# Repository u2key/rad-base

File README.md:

The PCB for LSI radiation irradiation test.
---

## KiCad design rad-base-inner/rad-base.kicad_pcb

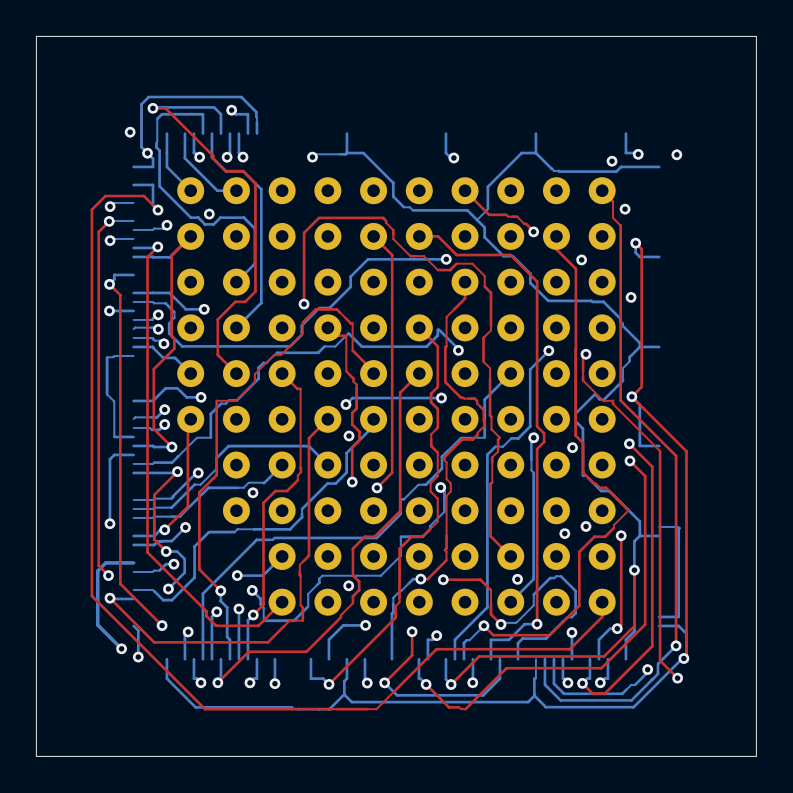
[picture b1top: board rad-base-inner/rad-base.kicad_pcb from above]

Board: 4 copper layers, 40.0 x 40.0 mm, 15 parts (1 on the bottom side), 90 nets.

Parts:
U1: S1D13513F01A100; QFP208-28X28MM
U2, U3, U4: 2x1
U5, U6, U7, U8, U9, U10, U11, U12, U13, U14, U15: 8x1

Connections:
GND: U1.2 (DB14), U1.12 (DB6), U1.22 (~WE0), U1.31 (~WAIT), U1.41 (OSCO1), U1.51 (VCP2(NC)), U1.54 (FPDAT16), U1.64 (FPDAT8), U1.74 (FPDAT0), U1.83 (GPIOG2), U1.93 (GPIOB7), U1.103 (TDO), U1.106 (GND@8), U1.116 (GPIOD2), U1.126 (CNF4), U1.135 (MEMDQM1), U1.145 (MEMBA0), U1.155 (MEMDQ12), U1.158 (MEMDQ11), U1.168 (HVDD5@4), U1.178 (MEMA5), U1.187 (AB18), U1.197 (GND@17), U1.207 (AB0), U2.1 (A1), U2.2 (A2)
VCC1: U1.1 (DB15), U1.21 (BUSCLK), U1.42 (OSCGND1), U1.53 (FPDAT17), U1.73 (FPDAT1), U1.94 (GPIOB6), U1.105 (HVDD4@1), U1.125 (CNF5), U1.146 (MEMA11), U1.157 (COREVDD@6), U1.177 (MEMA6), U1.198 (AB9), U3.1 (A1), U3.2 (A2)
VCC2: U1.11 (DB7), U1.32 (~RESET), U1.52 (PLLGND2), U1.63 (FPDAT9), U1.84 (GPIOG1), U1.104 (TRST), U1.115 (GPIOD3), U1.136 (MEMDQM0), U1.156 (COREVDD@5), U1.167 (MEMDQ4), U1.188 (AB17), U1.208 (COREVDD@7), U4.1 (A1), U4.2 (A2)
w1: U1.3 (DB13), U5.1 (A1)
w2: U1.4 (DB12), U5.2 (A2)
w3: U1.5 (DB11), U5.3 (A3)
w4: U1.6 (DB10), U5.4 (A4)
w5: U1.7 (DB9), U5.5 (A5)
w6: U1.8 (DB8), U5.6 (A6)
w7: U1.9 (HVDD1@0), U5.7 (A7)
w8: U1.10 (GND@0), U5.8 (A8)
w9: U1.13 (DB5), U6.1 (A1)
w10: U1.14 (DB4), U6.2 (A2)
w11: U1.15 (DB3), U6.3 (A3)
w12: U1.16 (DB2), U6.4 (A4)
w13: U1.17 (DB1), U6.5 (A5)
w14: U1.18 (DB0), U6.6 (A6)
w15: U1.19 (HVDD1@1), U6.7 (A7)
w16: U1.20 (GND@1), U6.8 (A8)
w17: U1.23 (~WE1), U7.1 (A1)
w18: U1.24 (M/~R), U7.2 (A2)
w19: U1.25 (~CS), U7.3 (A3)
w20: U1.26 (~BS), U7.4 (A4)
w21: U1.27 (RD/~WR), U7.5 (A5)
w22: U1.28 (~RD), U7.6 (A6)
w23: U1.29 (COREVDD@0), U7.7 (A7)
w24: U1.30 (~INT1), U7.8 (A8)
w26: U1.34 (~BURST), U8.2 (A2)
w27: U1.35 (~BDIP), U8.3 (A3)
w28: U1.36 (CLKI3), U8.4 (A4)
w29: U1.37 (COREVDD@1), U8.5 (A5)
w30: U1.38 (GND@2), U8.6 (A6)
w31: U1.39 (OSCVDD1), U8.7 (A7)
w32: U1.40 (OSCI1), U8.8 (A8)
w33: U1.43 (OSCGND2), U9.1 (A1)
w34: U1.44 (OSCO2), U9.2 (A2)
w35: U1.45 (OSCI2), U9.3 (A3)
w36: U1.46 (OSCVCC2), U9.4 (A4)
w37: U1.47 (PLLGND1), U9.5 (A5)
w38: U1.48 (VCP1(NC)), U9.6 (A6)
w39: U1.49 (PLLVDD1), U9.7 (A7)
w40: U1.50 (PLLVDD2), U9.8 (A8)
w41: U1.55 (FPDAT15), U10.1 (A1)
w42: U1.56 (FPDAT14), U10.2 (A2)
w43: U1.57 (HVDD2@0), U10.3 (A3)
w44: U1.58 (GND@3), U10.4 (A4)
w45: U1.59 (FPDAT13), U10.5 (A5)
w46: U1.60 (FPDAT12), U10.6 (A6)
w47: U1.61 (FPDAT11), U10.7 (A7)
w48: U1.62 (FPDAT10), U10.8 (A8)
w49: U1.65 (HVDD2@1), U11.1 (A1)
w50: U1.66 (GND@4), U11.2 (A2)
w51: U1.67 (FPDAT7), U11.3 (A3)
w52: U1.68 (FPDAT6), U11.4 (A4)
w53: U1.69 (FPDAT5), U11.5 (A5)
w54: U1.70 (FPDAT4), U11.6 (A6)
w55: U1.71 (FPDAT3), U11.7 (A7)
w56: U1.72 (FPDAT2), U11.8 (A8)
w57: U1.75 (HVDD2@2), U12.1 (A1)
w58: U1.76 (GND@5), U12.2 (A2)
w59: U1.77 (FPSHIFT), U12.3 (A3)
w60: U1.78 (FPFRAME), U12.4 (A4)
w61: U1.79 (FPLINE), U12.5 (A5)
w62: U1.80 (FPDRDY), U12.6 (A6)
w63: U1.81 (GPIOG4), U12.7 (A7)
w64: U1.82 (GPIOG3), U12.8 (A8)
w65: U1.85 (GPIOG0), U13.1 (A1)
w66: U1.86 (COREVDD@2), U13.2 (A2)
w67: U1.87 (GPIOA7), U13.3 (A3)
w68: U1.88 (GPIOA6), U13.4 (A4)
w69: U1.89 (GPIOA5), U13.5 (A5)
w70: U1.90 (GPIOA4), U13.6 (A6)
w71: U1.91 (HVDD3), U13.7 (A7)
w72: U1.92 (GND@6), U13.8 (A8)
w73: U1.95 (GPIOB5), U14.1 (A1)
w74: U1.96 (GPIOB4), U14.2 (A2)
w75: U1.97 (COREVDD@3), U14.3 (A3)
w76: U1.98 (HVDD4@0), U14.4 (A4)
w77: U1.99 (GND@7), U14.5 (A5)
w78: U1.100 (TCK), U14.6 (A6)
w79: U1.101 (TMS), U14.7 (A7)
w80: U1.102 (TDI), U14.8 (A8)
w81: U1.107 (GPIOC7), U15.1 (A1)
w82: U1.108 (GPIOC6), U15.2 (A2)
w83: U1.109 (GPIOC5), U15.3 (A3)
w84: U1.110 (GPIOC4), U15.4 (A4)
w85: U1.111 (GPIOC3), U15.5 (A5)
w86: U1.112 (GPIOC2), U15.6 (A6)
w87: U1.113 (GPIOC1), U15.7 (A7)
w88: U1.114 (GPIOC0), U15.8 (A8)

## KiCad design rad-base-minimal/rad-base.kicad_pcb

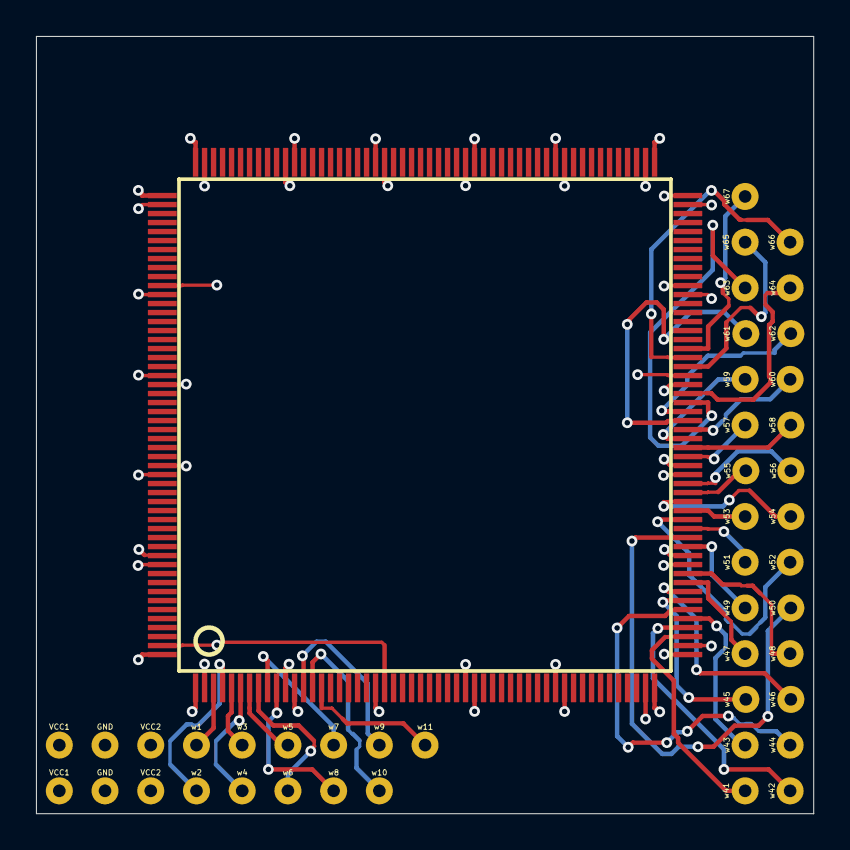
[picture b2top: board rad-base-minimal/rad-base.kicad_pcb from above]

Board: 4 copper layers, 43.2 x 43.2 mm, 45 parts (0 on the bottom side), 41 nets.

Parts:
U1: S1D13513F01A100; QFP208-28X28MM
U16, U17, U18, U19, U20, U21, U22, U23, U24, U25, U26, U27, U28, U29, U30, U31, U32, U62, U63, U64, U65, U66, U67, U68, U69, U70, U71, U72, U73, U74, U75, U76, U77, U78, U79, U80, U81, U82, U83, U84, U85, U86, U87, U88: 1x1

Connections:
GND: U1.2 (DB14), U1.12 (DB6), U1.22 (~WE0), U1.31 (~WAIT), U1.41 (OSCO1), U1.51 (VCP2(NC)), U1.54 (FPDAT16), U1.64 (FPDAT8), U1.74 (FPDAT0), U1.83 (GPIOG2), U1.93 (GPIOB7), U1.103 (TDO), U1.106 (GND@8), U1.116 (GPIOD2), U1.126 (CNF4), U1.135 (MEMDQM1), U1.145 (MEMBA0), U1.155 (MEMDQ12), U1.158 (MEMDQ11), U1.168 (HVDD5@4), U1.178 (MEMA5), U1.187 (AB18), U1.197 (GND@17), U1.207 (AB0), U16.1 (A1_1), U17.1 (A1_1)
VCC1: U1.1 (DB15), U1.21 (BUSCLK), U1.42 (OSCGND1), U1.53 (FPDAT17), U1.73 (FPDAT1), U1.94 (GPIOB6), U1.105 (HVDD4@1), U1.125 (CNF5), U1.146 (MEMA11), U1.157 (COREVDD@6), U1.177 (MEMA6), U1.198 (AB9), U18.1 (A1_1), U19.1 (A1_1)
VCC2: U1.11 (DB7), U1.32 (~RESET), U1.52 (PLLGND2), U1.63 (FPDAT9), U1.84 (GPIOG1), U1.104 (TRST), U1.115 (GPIOD3), U1.136 (MEMDQM0), U1.156 (COREVDD@5), U1.167 (MEMDQ4), U1.188 (AB17), U1.208 (COREVDD@7), U20.1 (A1_1), U21.1 (A1_1)
w1: U1.3 (DB13), U22.1 (A1_1)
w2: U1.4 (DB12), U23.1 (A1_1)
w3: U1.5 (DB11), U24.1 (A1_1)
w4: U1.6 (DB10), U25.1 (A1_1)
w5: U1.7 (DB9), U26.1 (A1_1)
w6: U1.8 (DB8), U27.1 (A1_1)
w7: U1.9 (HVDD1@0), U28.1 (A1_1)
w8: U1.10 (GND@0), U29.1 (A1_1)
w9: U1.13 (DB5), U30.1 (A1_1)
w10: U1.14 (DB4), U31.1 (A1_1)
w11: U1.15 (DB3), U32.1 (A1_1)
w41: U1.55 (FPDAT15), U62.1 (A1_1)
w42: U1.56 (FPDAT14), U63.1 (A1_1)
w43: U1.57 (HVDD2@0), U64.1 (A1_1)
w44: U1.58 (GND@3), U65.1 (A1_1)
w45: U1.59 (FPDAT13), U66.1 (A1_1)
w46: U1.60 (FPDAT12), U67.1 (A1_1)
w47: U1.61 (FPDAT11), U68.1 (A1_1)
w48: U1.62 (FPDAT10), U69.1 (A1_1)
w49: U1.65 (HVDD2@1), U70.1 (A1_1)
w50: U1.66 (GND@4), U71.1 (A1_1)
w51: U1.67 (FPDAT7), U72.1 (A1_1)
w52: U1.68 (FPDAT6), U73.1 (A1_1)
w53: U1.69 (FPDAT5), U74.1 (A1_1)
w54: U1.70 (FPDAT4), U75.1 (A1_1)
w55: U1.71 (FPDAT3), U76.1 (A1_1)
w56: U1.72 (FPDAT2), U77.1 (A1_1)
w57: U1.75 (HVDD2@2), U78.1 (A1_1)
w58: U1.76 (GND@5), U79.1 (A1_1)
w59: U1.77 (FPSHIFT), U80.1 (A1_1)
w60: U1.78 (FPFRAME), U81.1 (A1_1)
w61: U1.79 (FPLINE), U82.1 (A1_1)
w62: U1.80 (FPDRDY), U83.1 (A1_1)
w63: U1.81 (GPIOG4), U84.1 (A1_1)
w64: U1.82 (GPIOG3), U85.1 (A1_1)
w65: U1.85 (GPIOG0), U86.1 (A1_1)
w66: U1.86 (COREVDD@2), U87.1 (A1_1)
w67: U1.87 (GPIOA7), U88.1 (A1_1)

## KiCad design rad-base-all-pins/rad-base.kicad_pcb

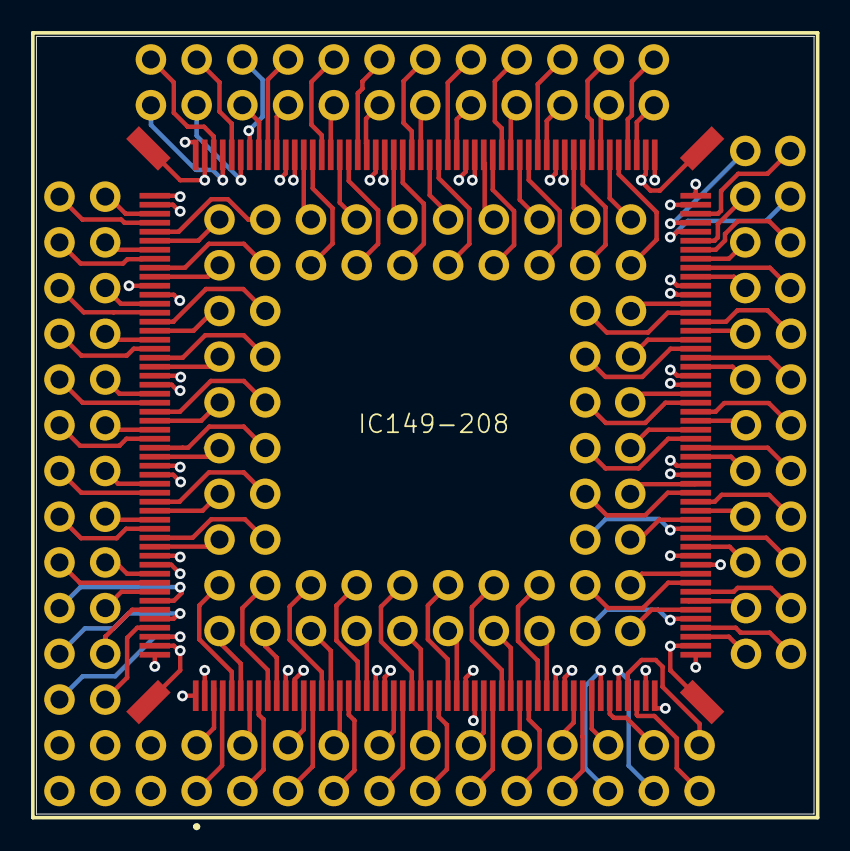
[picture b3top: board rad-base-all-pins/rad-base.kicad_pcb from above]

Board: 4 copper layers, 43.2 x 43.2 mm, 167 parts (0 on the bottom side), 163 nets.

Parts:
J1: IC149-208-161-B5; IC149208061B5
U16, U17, U18, U19, U20, U21, U22, U23, U24, U25, U26, U27, U28, U29, U30, U31, U32, U33, U34, U35, U36, U37, U38, U39, U40, U41, U42, U43, U44, U45, U46, U47, U48, U49, U50, U51, U52, U53, U54, U55, U56, U57, U58, U59, U60, U61, U62, U63, U64, U65, U66, U67, U68, U69, U70, U71, U72, U73, U74, U75, U76, U77, U78, U79, U80, U81, U82, U83, U84, U85, U86, U87, U88, U89, U90, U91, U92, U93, U94, U95, U96, U97, U98, U99, U100, U101, U102, U103, U104, U105, U106, U107, U108, U109, U110, U111, U112, U113, U114, U115, U116, U117, U118, U119, U120, U121, U122, U123, U124, U125, U126, U127, U128, U129, U130, U131, U132, U133, U134, U135, U136, U137, U138, U139, U140, U141, U142, U143, U144, U145, U146, U147, U148, U149, U150, U151, U152, U153, U154, U155, U156, U157, U158, U159, U160, U161, U162, U163, U164, U165, U166, U167, U168, U169, U170, U171, U172, U173, U174, U175, U176, U177, U178, U179, U180, U181: 1x1

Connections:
GND: J1.2, J1.12, J1.22, J1.31, J1.41, J1.51, J1.54, J1.64, J1.74, J1.83, J1.93, J1.103, J1.106, J1.116, J1.126, J1.135, J1.145, J1.155, J1.158, J1.168, J1.178, J1.187, J1.197, J1.207, J1.209, J1.210, J1.211, J1.212, U16.1 (A1_1), U17.1 (A1_1)
VCC1: J1.1, J1.21, J1.42, J1.53, J1.73, J1.94, J1.105, J1.125, J1.146, J1.157, J1.177, J1.198, U18.1 (A1_1), U19.1 (A1_1)
VCC2: J1.11, J1.32, J1.52, J1.63, J1.84, J1.104, J1.115, J1.136, J1.156, J1.167, J1.188, J1.208, U20.1 (A1_1), U21.1 (A1_1)
w1: J1.3, U22.1 (A1_1)
w2: J1.4, U23.1 (A1_1)
w3: J1.5, U24.1 (A1_1)
w4: J1.6, U25.1 (A1_1)
w5: J1.7, U26.1 (A1_1)
w6: J1.8, U27.1 (A1_1)
w7: J1.9, U28.1 (A1_1)
w8: J1.10, U29.1 (A1_1)
w9: J1.13, U30.1 (A1_1)
w10: J1.14, U31.1 (A1_1)
w11: J1.15, U32.1 (A1_1)
w12: J1.16, U33.1 (A1_1)
w13: J1.17, U34.1 (A1_1)
w14: J1.18, U35.1 (A1_1)
w15: J1.19, U36.1 (A1_1)
w16: J1.20, U37.1 (A1_1)
w17: J1.23, U38.1 (A1_1)
w18: J1.24, U39.1 (A1_1)
w19: J1.25, U40.1 (A1_1)
w20: J1.26, U41.1 (A1_1)
w21: J1.27, U42.1 (A1_1)
w22: J1.28, U43.1 (A1_1)
w23: J1.29, U44.1 (A1_1)
w24: J1.30, U45.1 (A1_1)
w25: J1.33, U46.1 (A1_1)
w26: J1.34, U47.1 (A1_1)
w27: J1.35, U48.1 (A1_1)
w28: J1.36, U49.1 (A1_1)
w29: J1.37, U50.1 (A1_1)
w30: J1.38, U51.1 (A1_1)
w31: J1.39, U52.1 (A1_1)
w32: J1.40, U53.1 (A1_1)
w33: J1.43, U54.1 (A1_1)
w34: J1.44, U55.1 (A1_1)
w35: J1.45, U56.1 (A1_1)
w36: J1.46, U57.1 (A1_1)
w37: J1.47, U58.1 (A1_1)
w38: J1.48, U59.1 (A1_1)
w39: J1.49, U60.1 (A1_1)
w40: J1.50, U61.1 (A1_1)
w41: J1.55, U62.1 (A1_1)
w42: J1.56, U63.1 (A1_1)
w43: J1.57, U64.1 (A1_1)
w44: J1.58, U65.1 (A1_1)
w45: J1.59, U66.1 (A1_1)
w46: J1.60, U67.1 (A1_1)
w47: J1.61, U68.1 (A1_1)
w48: J1.62, U69.1 (A1_1)
w49: J1.65, U70.1 (A1_1)
w50: J1.66, U71.1 (A1_1)
w51: J1.67, U72.1 (A1_1)
w52: J1.68, U73.1 (A1_1)
w53: J1.69, U74.1 (A1_1)
w54: J1.70, U75.1 (A1_1)
w55: J1.71, U76.1 (A1_1)
w56: J1.72, U77.1 (A1_1)
w57: J1.75, U78.1 (A1_1)
w58: J1.76, U79.1 (A1_1)
w59: J1.77, U80.1 (A1_1)
w60: J1.78, U81.1 (A1_1)
w61: J1.79, U82.1 (A1_1)
w62: J1.80, U83.1 (A1_1)
w63: J1.81, U84.1 (A1_1)
w64: J1.82, U85.1 (A1_1)
w65: J1.85, U86.1 (A1_1)
w66: J1.86, U87.1 (A1_1)
w67: J1.87, U88.1 (A1_1)
w68: J1.88, U89.1 (A1_1)
w69: J1.89, U90.1 (A1_1)
w70: J1.90, U91.1 (A1_1)
w71: J1.91, U92.1 (A1_1)
w72: J1.92, U93.1 (A1_1)
w73: J1.95, U94.1 (A1_1)
w74: J1.96, U95.1 (A1_1)
w75: J1.97, U96.1 (A1_1)
w76: J1.98, U97.1 (A1_1)
w77: J1.99, U98.1 (A1_1)
w78: J1.100, U99.1 (A1_1)
w79: J1.101, U100.1 (A1_1)
w80: J1.102, U101.1 (A1_1)
w81: J1.107, U102.1 (A1_1)
w82: J1.108, U103.1 (A1_1)
w83: J1.109, U104.1 (A1_1)
w84: J1.110, U105.1 (A1_1)
w85: J1.111, U106.1 (A1_1)
w86: J1.112, U107.1 (A1_1)
w87: J1.113, U108.1 (A1_1)
w88: J1.114, U109.1 (A1_1)
w89: J1.117, U110.1 (A1_1)
w90: J1.118, U111.1 (A1_1)
w91: J1.119, U112.1 (A1_1)
w92: J1.120, U113.1 (A1_1)
w93: J1.121, U114.1 (A1_1)
w94: J1.122, U115.1 (A1_1)
w95: J1.123, U116.1 (A1_1)
w96: J1.124, U117.1 (A1_1)
w97: J1.127, U118.1 (A1_1)
w98: J1.128, U119.1 (A1_1)
w99: J1.129, U120.1 (A1_1)
w100: J1.130, U121.1 (A1_1)
w101: J1.131, U122.1 (A1_1)
w102: J1.132, U123.1 (A1_1)
w103: J1.133, U124.1 (A1_1)
w104: J1.134, U125.1 (A1_1)
w105: J1.137, U126.1 (A1_1)
w106: J1.138, U127.1 (A1_1)
w107: J1.139, U128.1 (A1_1)
w108: J1.140, U129.1 (A1_1)
w109: J1.141, U130.1 (A1_1)
w110: J1.142, U131.1 (A1_1)
w111: J1.143, U132.1 (A1_1)
w112: J1.144, U133.1 (A1_1)
w113: J1.147, U134.1 (A1_1)
w114: J1.148, U135.1 (A1_1)
w115: J1.149, U136.1 (A1_1)
w116: J1.150, U137.1 (A1_1)
w117: J1.151, U138.1 (A1_1)
w118: J1.152, U139.1 (A1_1)
w119: J1.153, U140.1 (A1_1)
w120: J1.154, U141.1 (A1_1)
w121: J1.159, U142.1 (A1_1)
w122: J1.160, U143.1 (A1_1)
w123: J1.161, U144.1 (A1_1)
w124: J1.162, U145.1 (A1_1)
w125: J1.163, U146.1 (A1_1)
w126: J1.164, U147.1 (A1_1)
w127: J1.165, U148.1 (A1_1)
w128: J1.166, U149.1 (A1_1)
w129: J1.169, U150.1 (A1_1)
w130: J1.170, U151.1 (A1_1)
w131: J1.171, U152.1 (A1_1)
w132: J1.172, U153.1 (A1_1)
w133: J1.173, U154.1 (A1_1)
w134: J1.174, U155.1 (A1_1)
w135: J1.175, U156.1 (A1_1)
w136: J1.176, U157.1 (A1_1)
w137: J1.179, U158.1 (A1_1)
w138: J1.180, U159.1 (A1_1)
w139: J1.181, U160.1 (A1_1)
w140: J1.182, U161.1 (A1_1)
w141: J1.183, U162.1 (A1_1)
w142: J1.184, U163.1 (A1_1)
w143: J1.185, U164.1 (A1_1)
w144: J1.186, U165.1 (A1_1)
w145: J1.189, U166.1 (A1_1)
w146: J1.190, U167.1 (A1_1)
w147: J1.191, U168.1 (A1_1)
w148: J1.192, U169.1 (A1_1)
w149: J1.193, U170.1 (A1_1)
w150: J1.194, U171.1 (A1_1)
w151: J1.195, U172.1 (A1_1)
w152: J1.196, U173.1 (A1_1)
w153: J1.199, U174.1 (A1_1)
w154: J1.200, U175.1 (A1_1)
w155: J1.201, U176.1 (A1_1)
w156: J1.202, U177.1 (A1_1)
w157: J1.203, U178.1 (A1_1)
w158: J1.204, U179.1 (A1_1)
w159: J1.205, U180.1 (A1_1)
w160: J1.206, U181.1 (A1_1)
